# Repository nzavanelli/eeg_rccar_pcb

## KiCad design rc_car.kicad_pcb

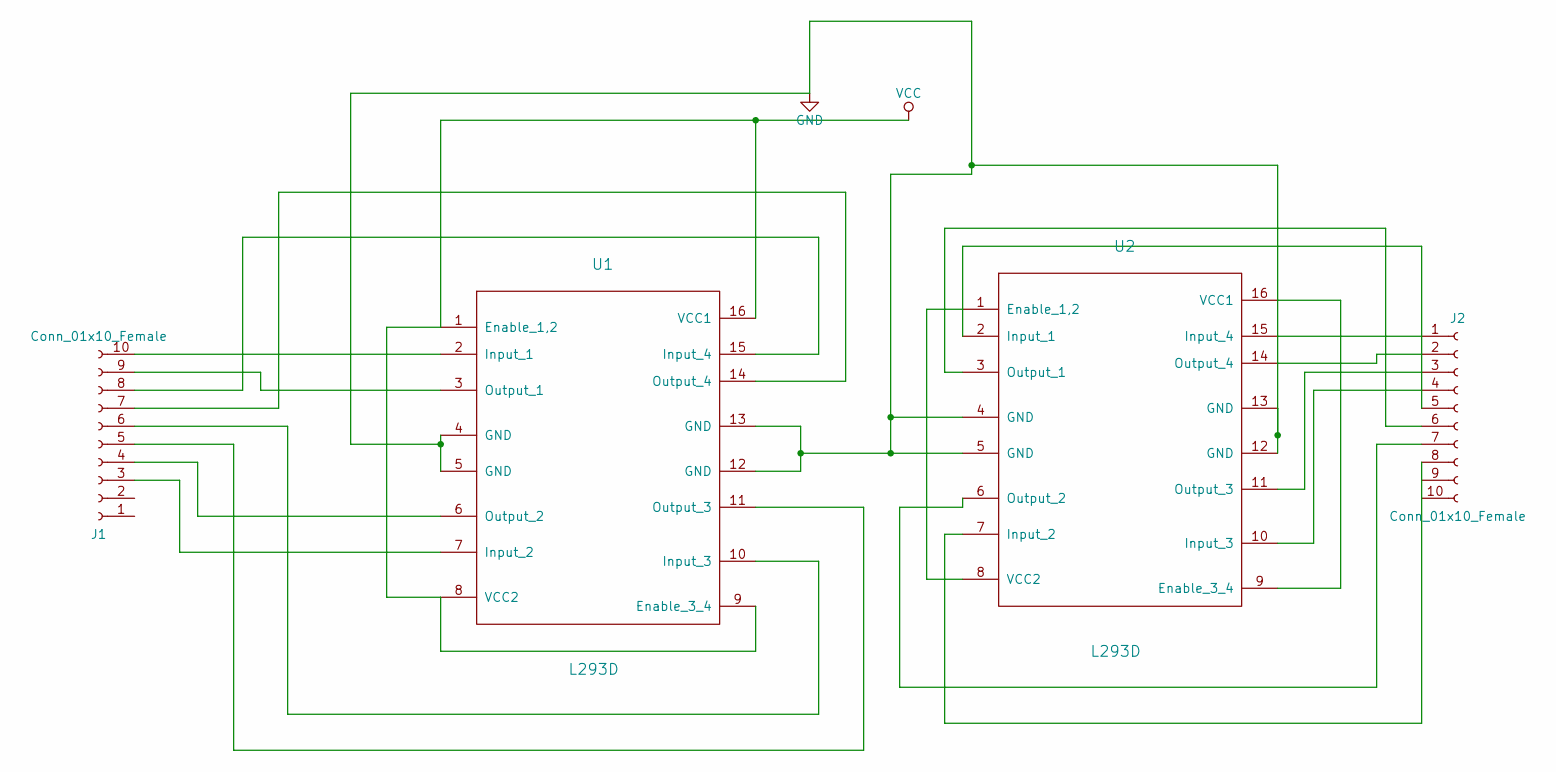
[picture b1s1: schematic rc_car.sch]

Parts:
J1, J2: Conn_01x10_Female; Socket_Strip_Angled_1x01_Pitch2.00mm
U1, U2: L293D; Pin_Header_Angled_2x16_Pitch1.00mm

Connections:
GND: U1.4 (GND), U1.5 (GND), U1.12 (GND), U1.13 (GND), U2.4 (GND), U2.5 (GND), U2.12 (GND), U2.13 (GND)
unnamed: J1.3, U1.7 (Input_2)
unnamed: J1.4, U1.6 (Output_2)
unnamed: J1.5, U1.11 (Output_3)
unnamed: J1.6, U1.10 (Input_3)
unnamed: J1.7, U1.14 (Output_4)
unnamed: J1.8, U1.15 (Input_4)
unnamed: J1.9, U1.3 (Output_1)
unnamed: J1.10, U1.2 (Input_1)
unnamed: J2.1, U2.15 (Input_4)
unnamed: J2.2, U2.14 (Output_4)
unnamed: J2.3, U2.11 (Output_3)
unnamed: J2.4, U2.10 (Input_3)
unnamed: J2.5, U2.2 (Input_1)
unnamed: J2.6, U2.3 (Output_1)
unnamed: J2.7, U2.6 (Output_2)
unnamed: J2.8, U2.7 (Input_2)
unnamed: U2.1 (Enable_1,2), U2.8 (VCC2)
unnamed: U2.9 (Enable_3_4), U2.16 (VCC1)
VCC: U1.1 (Enable_1,2), U1.8 (VCC2), U1.9 (Enable_3_4), U1.16 (VCC1)

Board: 2 copper layers, 4 parts (0 on the bottom side), 20 nets, no tracks yet.
